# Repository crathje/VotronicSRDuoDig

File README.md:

# Get data from Votronic SR Duo Digital and Votronic MPP / MPPT solar chargers

I am using a Votronic SR 300 Duo Digital with serial no. 13v20.0121 which is not capable of connecting the Votronic bluetooth devices (supported starting with serial no. 14Vxx.xxxxx):

In my RV it is connected to a Votronic Solar Computer S 1250 (again not capable of the bluetooth stuff which started with serial no. 15V40.xxxxx):

So I tried connecting a logic analyzer and found some flanks with the smaller ones beeing 980µs apart which seemed to be a bit length. I added a UART analyzer with 1020baud (1 / 0.000980 = 1020) and now I was able to see some bytes without any timing errors:

To verify the voltage I attached a digital storage oscilloscope and found a pretty solid 5V level output (1 y-unit = 1V): 

# Get data from Votronic MPP / MPPT solar chargers

After selling the above mentioned SR 300 Duo Digital along with the RV, I bought a Votronic MPP 430 Duo Digital for my new RV. The protocol is similar but contains e.g. the battery voltage as well which can come in quire handy. 

# Sample

Simple paltform IO project for esp32 using hardware serial: [basic-platformIO/src/main.cpp](examples/basic-platformIO/src/main.cpp).

No device at hand? Try: [arduinoNoDevice.ino](examples/arduinoNoDevice/arduinoNoDevice.ino).

# Pinout of the RJ12 6p6c connector

The most relevant pins would be :
1. Serial Data
2. Solar/Main Battery +
3. 
4. GND
5. 
6. 

# Schematics

[Eagle SCH](extras/VotronicSRDuoDig_connector.sch)

[Eagle BRD](extras/VotronicSRDuoDig_connector.brd)

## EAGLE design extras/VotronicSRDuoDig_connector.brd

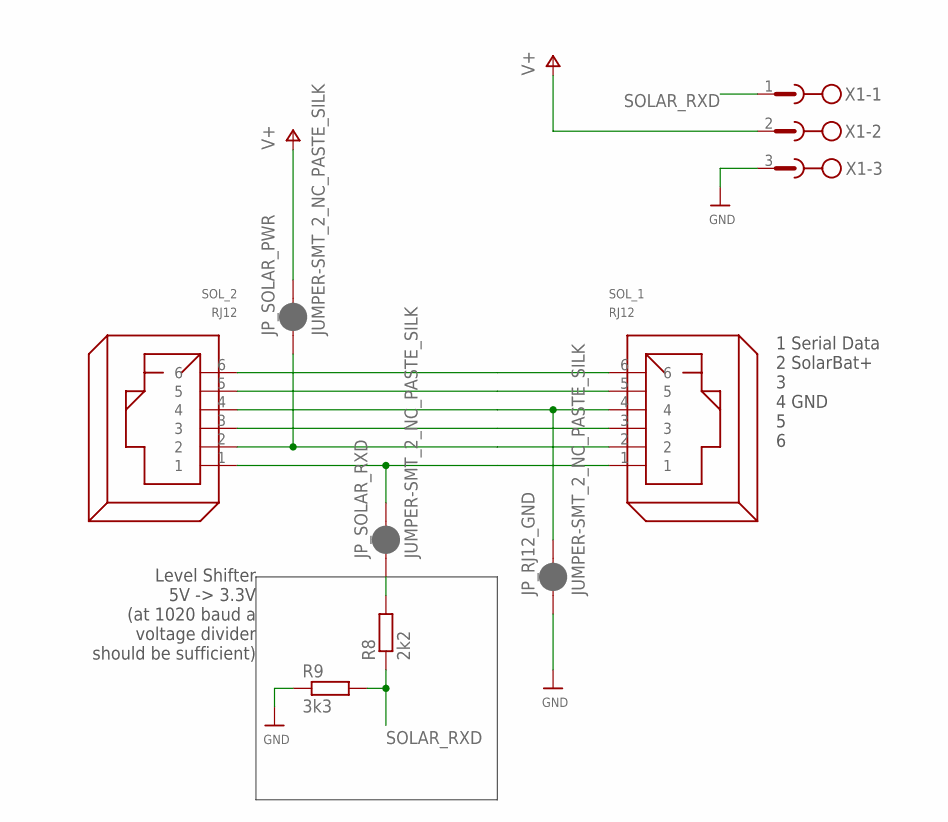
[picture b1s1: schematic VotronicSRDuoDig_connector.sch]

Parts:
JP_RJ12_GND: JUMPER-SMT_2_NC_PASTE_SILK; SMT-JUMPER_2_NC_PASTE_SILK
JP_SOLAR_PWR: JUMPER-SMT_2_NC_PASTE_SILK; SMT-JUMPER_2_NC_PASTE_SILK
JP_SOLAR_RXD: JUMPER-SMT_2_NC_PASTE_SILK; SMT-JUMPER_2_NC_PASTE_SILK
R8: 2k2; R0805
R9: 3k3; R0805
SOL_1, SOL_2: RJ12
X1: W232-3

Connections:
GND: JP_RJ12_GND.1, R9.1, X1.3
unnamed: JP_SOLAR_RXD.1, R8.2
unnamed: SOL_1.3, SOL_2.3
unnamed: JP_SOLAR_PWR.1, SOL_1.2, SOL_2.2
unnamed: JP_SOLAR_RXD.2, SOL_1.1, SOL_2.1
unnamed: SOL_1.5, SOL_2.5
unnamed: SOL_1.6, SOL_2.6
SOLAR_GND: JP_RJ12_GND.2, SOL_1.4, SOL_2.4
SOLAR_RXD: R8.1, R9.2, X1.1
V+: JP_SOLAR_PWR.2, X1.2

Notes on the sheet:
1 Serial Data 2 SolarBat+ 3 4 GND 5 6
Level Shifter 5V -> 3.3V (at 1020 baud a voltage divider should be sufficient)

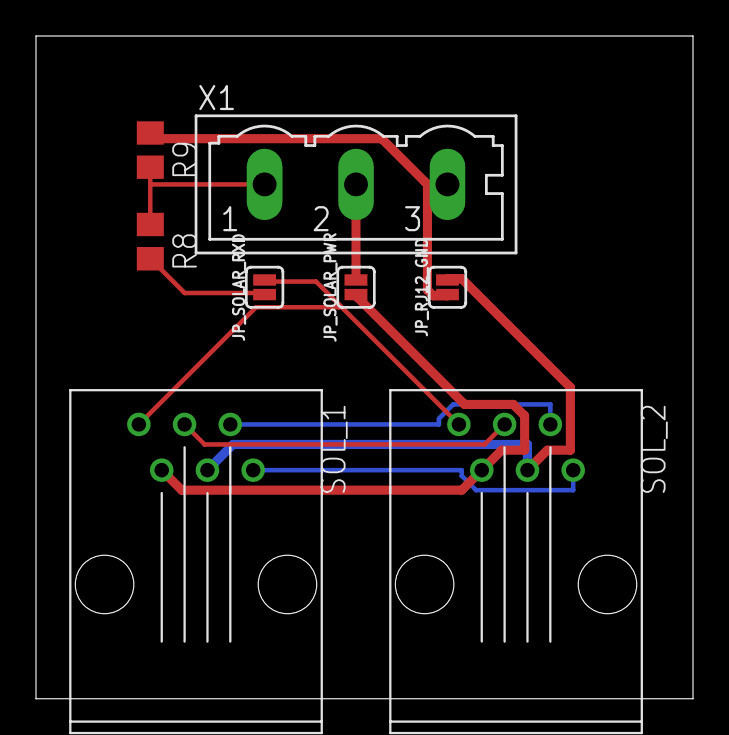
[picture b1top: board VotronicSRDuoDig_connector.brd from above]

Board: 2 copper layers, 36.5 x 36.8 mm, 8 parts (0 on the bottom side), 10 nets.

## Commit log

2020-10-20 Initital push (just reading current right now)
2021-04-04 fixed c 'n p mistake
2024-09-10 Add features from Votronic MPP 430.
2024-09-10 Correct spelling. Add missing . in path.

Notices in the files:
parts and their libraries:
SparkFun-Jumpers: Licensing: Creative Commons ShareAlike 4.0 International - https://creativecommons.org/licenses/by-sa/4.0
microbuilder: This work is placed in the public domain, and may be freely used for commercial and non-commercial work with the following conditions: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
